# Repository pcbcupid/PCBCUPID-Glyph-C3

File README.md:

# PCBCUPID-GLYPH-C3-PCB

This repo contains open source PCB files for PCBCUPID Glyph C3
This particular PCB is designed using Kicad v8.0

**This design has been built and tested successfully!**
For more details, check out the product pages at

   * [Glyph-C3](https://shop.pcbcupid.com/product/gd001/)

We are here to build India's largest open source hardware community, If you like to support
please consider buying the product from the above link!

[Creative Commons Attribution, Share-Alike license](https://creativecommons.org/licenses/by-sa/4.0/deed.en)
All text above must be included in any redistribution

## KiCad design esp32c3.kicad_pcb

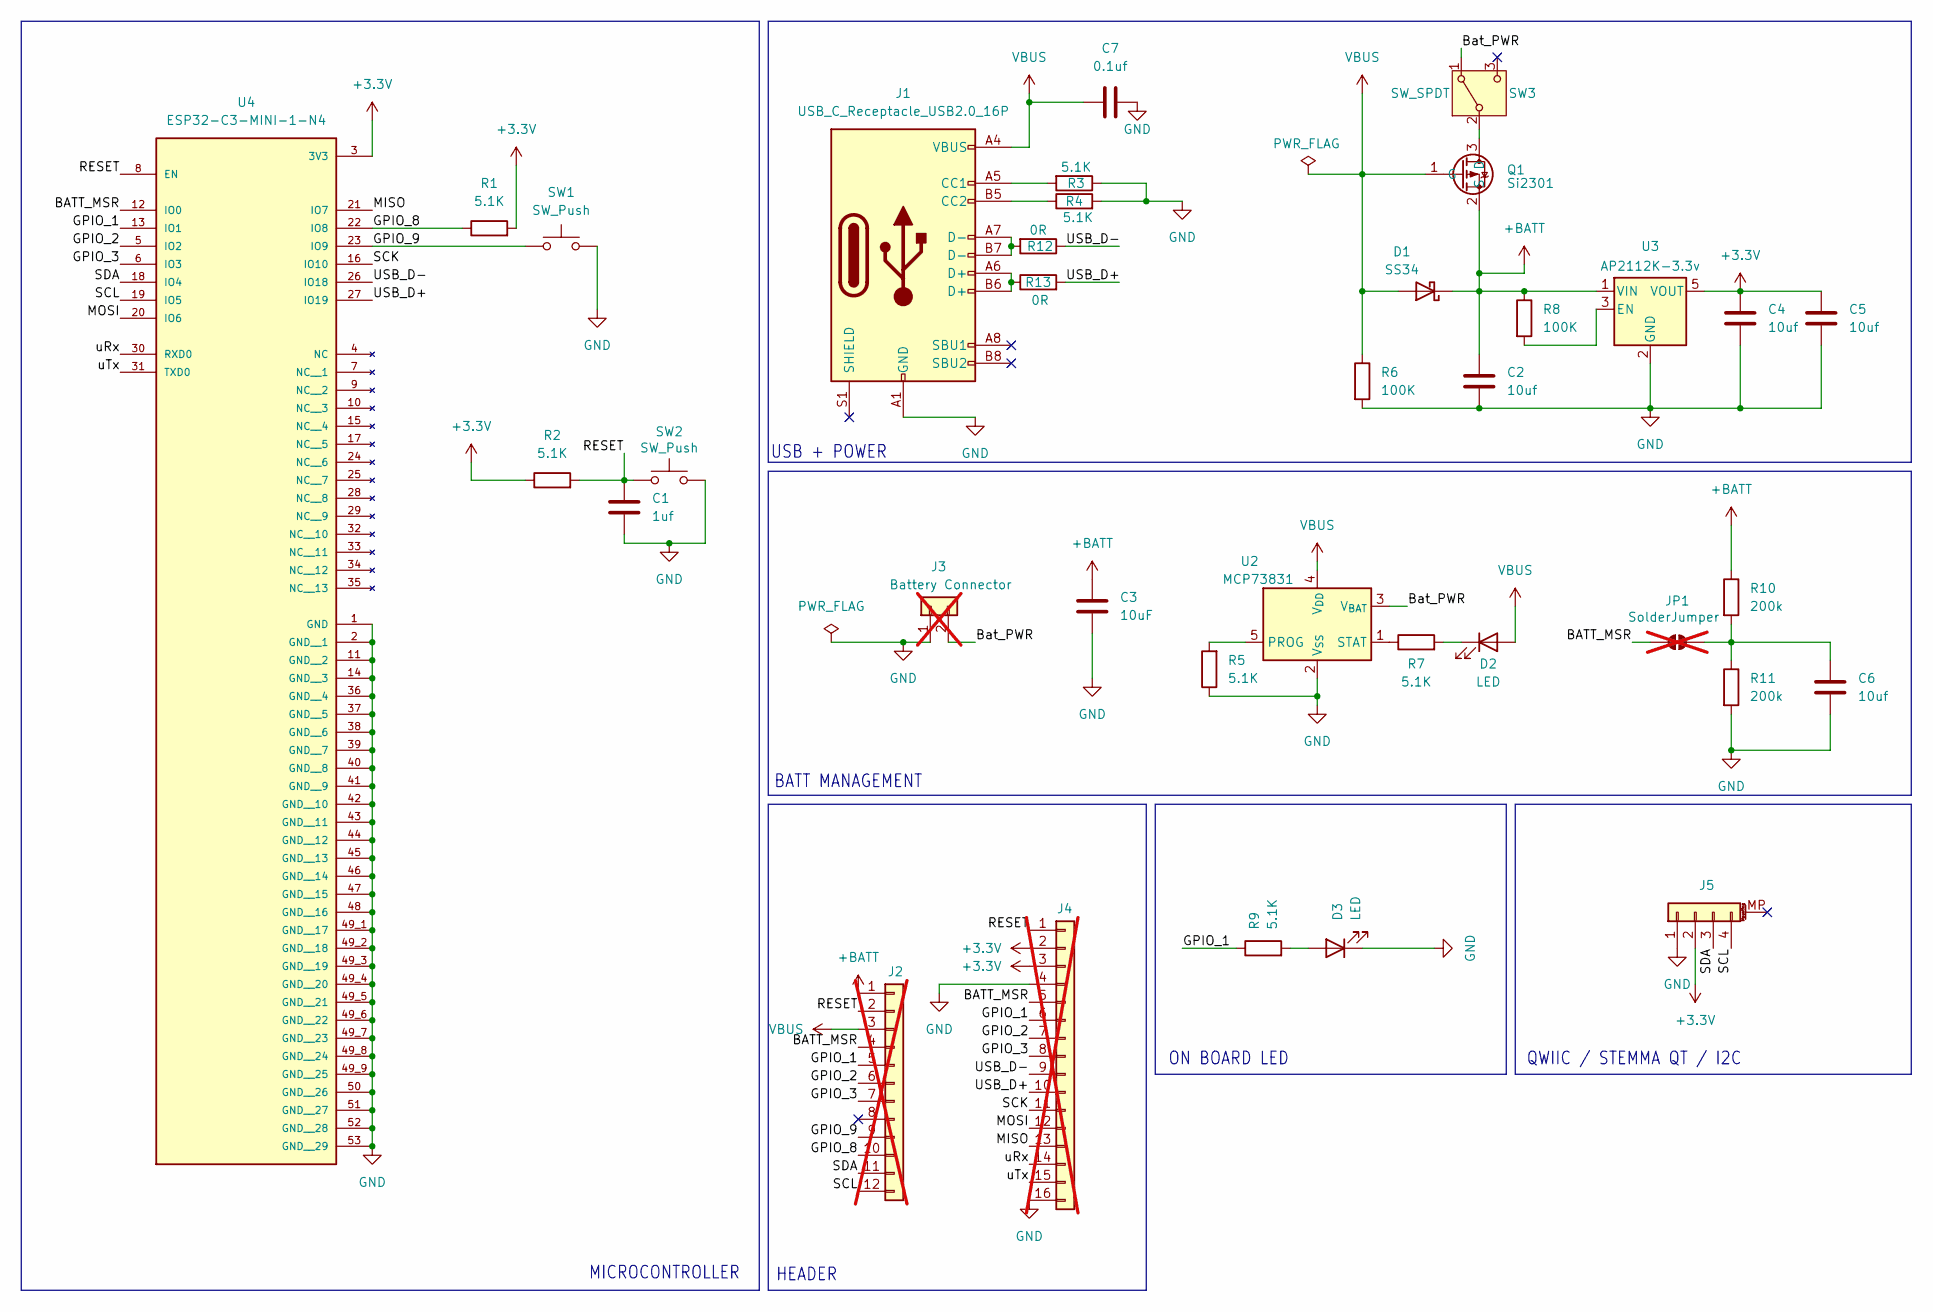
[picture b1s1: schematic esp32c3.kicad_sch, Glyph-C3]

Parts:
C1: 1uf; C_0603_1608Metric
C2, C4, C5, C6: 10uf; C_0603_1608Metric
C3: 10uF; C_0603_1608Metric
C7: 0.1uf; C_0603_1608Metric
D1: SS34; D_SMA
D2, D3: LED; LED_0603_1608Metric
J1: USB_C_Receptacle_USB2.0_16P; USB_C_Receptacle_Palconn_UTC16-G
J2: Conn_01x12; PinSocket_1x12_P2.54mm_Vertical; not fitted
J3: Battery Connector; TestPoint_01x02; not fitted
J4: Conn_01x16; PinSocket_1x16_P2.54mm_Vertical; not fitted
J5: Conn_01x04_MountingPin; JST_SH_BM04B-SRSS-TB_1x04-1MP_P1.00mm_Vertical
JP1: SolderJumper; SolderJumper-2_P1.3mm_Open_RoundedPad1.0x1.5mm; not fitted
Q1: Si2301; SOT-23
R1, R2, R3, R4, R5, R7, R9: 5.1K; R_0603_1608Metric
R6, R8: 100K; R_0603_1608Metric
R10, R11: 200k; R_0603_1608Metric
R12, R13: 0R; R_0603_1608Metric
SW1, SW2: SW_Push; SW_SPST_PTS810
SW3: SW_SPDT; SW_SPDT_PCM12
U2: MCP73831; SOT-23-5
U3: AP2112K-3.3v; SOT-23-5
U4: ESP32-C3-MINI-1-N4; ESP32-H2-MINI-1_EXP; PARTREV v1.0

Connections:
+3.3V: C4.1, C5.1, J4.2, J4.3, J5.2, R1.2, R2.1, U3.5 (VOUT), U4.3 (3V3)
+BATT: C2.1, C3.1, D1.1 (K), J2.1, Q1.2 (S), R8.1, R10.1, U3.1 (VIN)
/BATT_MSR: J2.4, J4.5, JP1.1 (A), U4.12 (IO0)
/Bat_PWR: J3.2, SW3.1 (A), U2.3 (V_{BAT})
/D+: J1.A6 (D+), J1.B6 (D+), R13.1
/D-: J1.A7 (D-), J1.B7 (D-), R12.2
/GPIO_1: J2.5, J4.6, R9.1, U4.13 (IO1)
/GPIO_2: J2.6, J4.7, U4.5 (IO2)
/GPIO_3: J2.7, J4.8, U4.6 (IO3)
/GPIO_8: J2.10, R1.1, U4.22 (IO8)
/GPIO_9: J2.9, SW1.1, U4.23 (IO9)
/MISO: J4.13, U4.21 (IO7)
/MOSI: J4.12, U4.20 (IO6)
/RESET: C1.1, J2.2, J4.1, R2.2, SW2.1, U4.8 (EN)
/SCK: J4.11, U4.16 (IO10)
/SCL: J2.12, J5.4, U4.19 (IO5)
/SDA: J2.11, J5.3, U4.18 (IO4)
/USB_D+: J4.10, R13.2, U4.27 (IO19)
/USB_D-: J4.9, R12.1, U4.26 (IO18)
/uRx: J4.14, U4.30 (RXD0)
/uTx: J4.15, U4.31 (TXD0)
GND: C1.2, C2.2, C3.2, C4.2, C5.2, C6.2, C7.2, D3.1 (K), J1.A1 (GND), J1.A12 (GND), J1.B1 (GND), J1.B12 (GND), J3.1, J4.4, J4.16, J5.1, R3.1, R4.2, R5.1, R6.2, R11.2, SW1.2, SW2.2, U2.2 (V_{SS}), U3.2 (GND), U4.1 (GND), U4.2 (GND__1), U4.11 (GND__2), U4.14 (GND__3), U4.36 (GND__4), U4.37 (GND__5), U4.38 (GND__6), U4.39 (GND__7), U4.40 (GND__8), U4.41 (GND__9), U4.42 (GND__10), U4.43 (GND__11), U4.44 (GND__12), U4.45 (GND__13), U4.46 (GND__14), U4.47 (GND__15), U4.48 (GND__16), U4.49_1 (GND__17), U4.49_2 (GND__18), U4.49_3 (GND__19), U4.49_4 (GND__20), U4.49_5 (GND__21), U4.49_6 (GND__22), U4.49_7 (GND__23), U4.49_8 (GND__24), U4.49_9 (GND__25), U4.50 (GND__26), U4.51 (GND__27), U4.52 (GND__28), U4.53 (GND__29)
unnamed: D2.1 (K), R7.2
unnamed: D3.2 (A), R9.2
unnamed: J1.A5 (CC1), R3.2
unnamed: J1.B5 (CC2), R4.1
unnamed: C6.1, JP1.2 (B), R10.2, R11.1
unnamed: Q1.3 (D), SW3.2 (B)
unnamed: R5.2, U2.5 (PROG)
unnamed: R7.1, U2.1 (STAT)
unnamed: R8.2, U3.3 (EN)
VBUS: C7.1, D1.2 (A), D2.2 (A), J1.A4 (VBUS), J1.A9 (VBUS), J1.B4 (VBUS), J1.B9 (VBUS), J2.3, Q1.1 (G), R6.1, U2.4 (V_{DD})

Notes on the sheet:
ON BOARD LED
HEADER
BATT MANAGEMENT
QWIIC / STEMMA QT / I2C
MICROCONTROLLER
USB + POWER

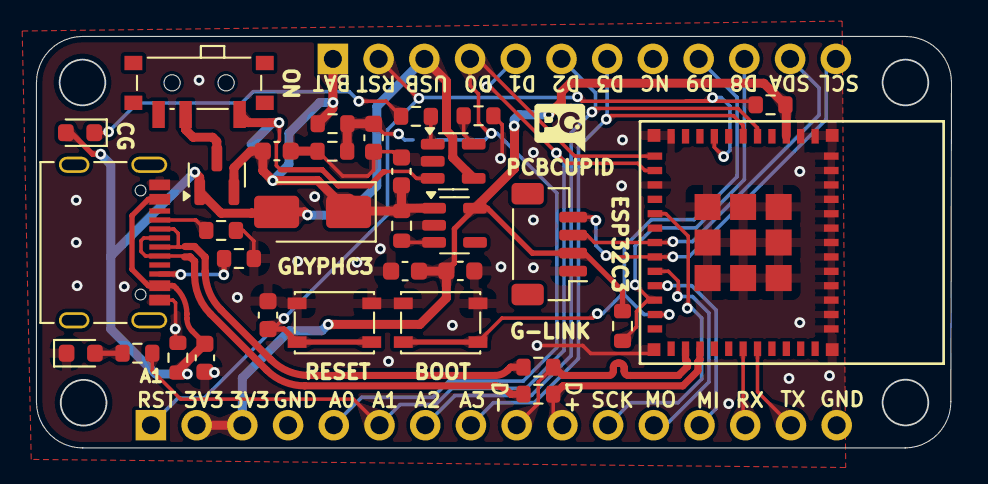
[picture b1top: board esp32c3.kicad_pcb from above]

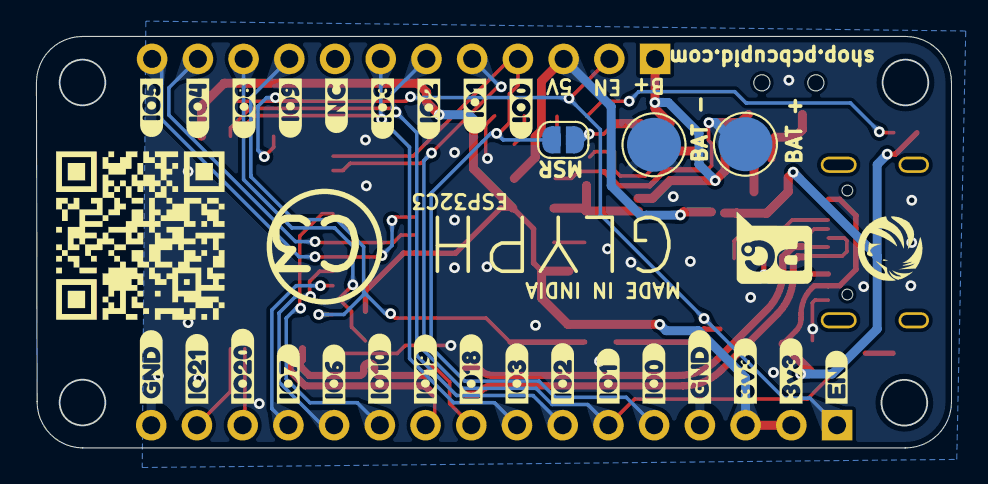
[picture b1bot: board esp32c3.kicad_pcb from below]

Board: 2 copper layers, 50.8 x 22.8 mm, 61 parts (28 on the bottom side), 32 nets.

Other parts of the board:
kibuzzard-668B7A0A: G***; kibuzzard-668B7A0A
kibuzzard-668B7A1E: G***; kibuzzard-668B7A1E
kibuzzard-668B7A2D: G***; kibuzzard-668B7A2D
kibuzzard-668B7A7C: G***; kibuzzard-668B7A7C
kibuzzard-668B7A62, kibuzzard-668B7A62#2: G***; kibuzzard-668B7A62
kibuzzard-668B79B7: G***; kibuzzard-668B79B7
kibuzzard-668B79F7: G***; kibuzzard-668B79F7
kibuzzard-668B789B, kibuzzard-668B789B#2: G***; kibuzzard-668B789B
kibuzzard-668B795C: G***; kibuzzard-668B795C
kibuzzard-668B797C: G***; kibuzzard-668B797C
kibuzzard-668B7879: G***; kibuzzard-668B7879
kibuzzard-668B7995: G***; kibuzzard-668B7995
kibuzzard-668CCB9F: G***; kibuzzard-668CCB9F
kibuzzard-668CCB83: G***; kibuzzard-668CCB83
kibuzzard-668CCC45: G***; kibuzzard-668CCC45
kibuzzard-668CCC52: G***; kibuzzard-668CCC52
kibuzzard-668CCD9D: G***; kibuzzard-668CCD9D
kibuzzard-668CCD74: G***; kibuzzard-668CCD74
kibuzzard-668CCD89: G***; kibuzzard-668CCD89
kibuzzard-668CCDA5: G***; kibuzzard-668CCDA5
kibuzzard-668CCDB1: G***; kibuzzard-668CCDB1
kibuzzard-668CE34C: G***; kibuzzard-668CE34C
kibuzzard-668CE341: G***; kibuzzard-668CE341

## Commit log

2024-09-05 Release v1.0.0
2024-09-05 added read.me

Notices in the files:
esp32c3.kicad_sch:
License : CC BY-SA
